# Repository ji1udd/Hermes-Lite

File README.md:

# <Font color="blue"> ji1udd Hermes-Lite Enhancement </font>
## 6M Frontend using undersampling technique  
Hermes-Lite v1.22 covers HF all bands.
Its sampling frequency(Fs) is 73.728MHz and the first nyquist zone is under 36.764MHz.
Hermes-Lite is a good performance system, but It does not support 6M band. 
I thought whether Hermes-Lite could be used on 6M band by using undersampling technique, without a transverter. 
But I have never seen any undersampling transmitters and transcevers.
I made 6M Test Frontend board for the performance test and to realized it. 

[_Schematic_](6M-Band/frontend_6M_v100/docs/frontend6m.pdf)
[_BOM_](6M-Band/frontend_6M_v100/docs/BOM_Frontend6m.pdf)
[_Gerber_](6M-Band/frontend_6M_v100/gerber/frontend6.zip)
[_Gerber-ReadMe_](6M-Band/frontend_6M_v100/gerber/ReadMe.txt)  
[_PCB Errata and filter adjustment_](6M-Band/frontend_6M_v100/docs/Frontend6m_v1.0_PCB_Errata_and_FilterAdjustment.pdf)

I got very good result. Here is the output power and IMD3 of 6M Test Frontend. 

This application takes advantage of 1st image signal ( Fs-Ftx ). 
Therefore, AD9866 interpolation should be off (1x).   

Other unnecessary spurs (e.g. 2Ftx) should be care.
In case of Hermes-Lite v1.22,  Fs is 73.728MHz. 2Ftx is out of 6M band. 2Ftx spur can be rejected by BPF perfectly.  

If Fs is 76.8MHz (Hermes-Lite v2 will use), 2Fx is in-band. 
It might be weak (<-65dBc) according to the current result.
But Fs=76.8MHz settign is not suitable for 6M.  

For more detail, refer to [_6M Support thread_](https://groups.google.com/forum/#!topic/hermes-lite/oetsCIdmZzY).

## Frontend v1.42 experiment with balanced 6M BPF.
I converted the single-ended 6M BPF that is used on 6M Frontend board to balanced-ended's in order to apply to Frontend v1.42 circuit.

I got the almost same result as 6M Frontend.

More result is [_here_.](6M-Band/frontend_v142_with_6M_filter/docs/6m_Spur_v142_and_orignal.pdf)

## Undersampling 6M transceiver (World's 1st?)
I made 6M transceiver using 6M Frontend. I added my new 6M power amplifier board. Its output power is 3W in CW.
In SSB mode, the output power should be kept under 1W for good IMD3 (under -35dBc) by adjusting Drive Level (TxPGA).
Rx Pre Amplifier on the schematic is not needed by adjusting AD9866 RxPGA.

[_Schematic_](6M-Band/PA_6M/docs/6mPA_v1.01.pdf)
[_BOM_](6M-Band/PA_6M/docs/BOM_6m_PA.pdf)
[_Gerber_] (6M-Band/PA_6M/gerber/amp6.zip)

## Audio Codec
As I have a sound trouble when PowerSDR VAC is used on my Windows8.1 PC, I added an external audio codec as a solid countermeasure.  
I got the audio codec information from [_ik1xpv web site_](http://www.steila.com/blog/index.php?controller=post&action=view&id_post=4).

[_Schematic_](audiocodec/docs/AudioCodec_v1.0.pdf)  
[_BOM_](audiocodec/docs/BOM_Keyer_AudioCodec.pdf)  
[_Gerber_](audiocodec/gerber/audiocodec.zip)  
[_Audio Codec board connection CVA9_](audiocodec/docs/Connector_Assignment_BeMicroCVA9_Keyer_AudioCodec.pdf)  
[_Mic jack jumper setting_](audiocodec/docs/Mic_Jack_jumper_setting.pdf)

Now, PowerSDR and piHPSDR works well with this audio codec board.

## Iambic keyer
I implemented  Iambic keyer functions that PowerSDR supports, except Keyer Mode-B. 
I implemented Keyer practice mode(Keyer is active, but does not transmit) instead of Mode-B. 
The keyer that I scratch built needs only 150 ALMs, 1 DSP block, 8K Byte block memory.

### Supported functions
- Variable Sidetone frequency :  
Sidetone is always synchronized with receiver pitch. I added two new ways of sidetone output.   
1) Square wave output for inexpensive piezo sounder.  
2) Sine wave output through an external audio codec.  
- Variable Speed control
- Others  
Keyer ON/OFF, Sidetone ON/OFF, Break in delay time, CW delay Key-Up,   
CW delay Key-Down,Reverse Paddles,Weight

[_Keyer installation diagram_](audiocodec/docs/IambicKeyer_installation_diagram.pdf)  
[_Keyer sequence and setting_](audiocodec/docs/Keyer_Sequece_and_setting.pdf)  
[_Modification of PCB (Schematic)_](audiocodec/docs/Modification_of_Audio_Codec_Board_for_keyer_schematic.pdf)  
[_Modification of PCB (photo)_](audiocodec/docs/Modification_of_Audio_Codec_Board_for_keyer.jpg)   
[_Keyer connection CVA9_](audiocodec/docs/Connector_Assignment_BeMicroCVA9_Keyer_AudioCodec.pdf)  
[_Keyer connection SDK (Not Verified Yet)_](audiocodec/docs/Connector_Assignment_BeMicroSDK_Keyer_AudioCodec.pdf)  

Verilog-HDL code was released on my git (27 July 2016).  

## Bemicro CVA9 100Base-TX connection
I modified the Hermes-Lite v1.22 firmware for connecting to Raspberry Pi / PiHPSDR directly. 

Verilog-HDL code was released on [_CVA9-100Base-TX branch_](https://github.com/ji1udd/Hermes-Lite/tree/CVA9-100Base-TX) (5 May 2017).

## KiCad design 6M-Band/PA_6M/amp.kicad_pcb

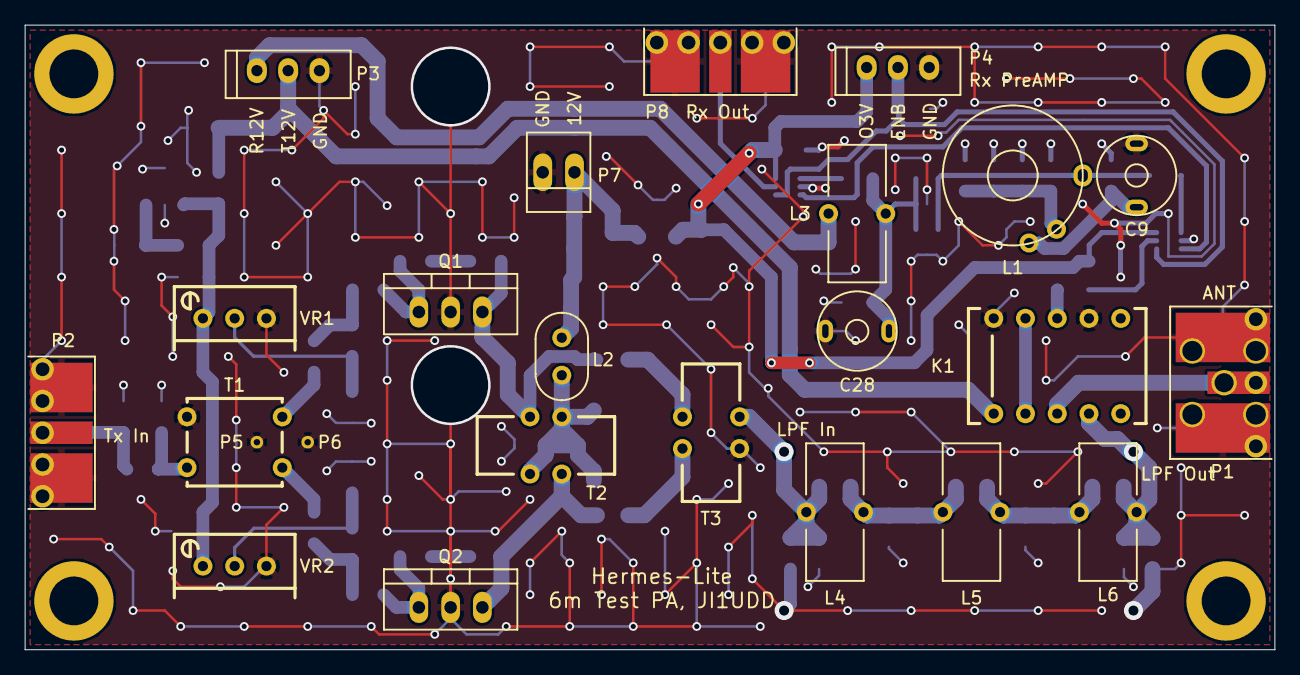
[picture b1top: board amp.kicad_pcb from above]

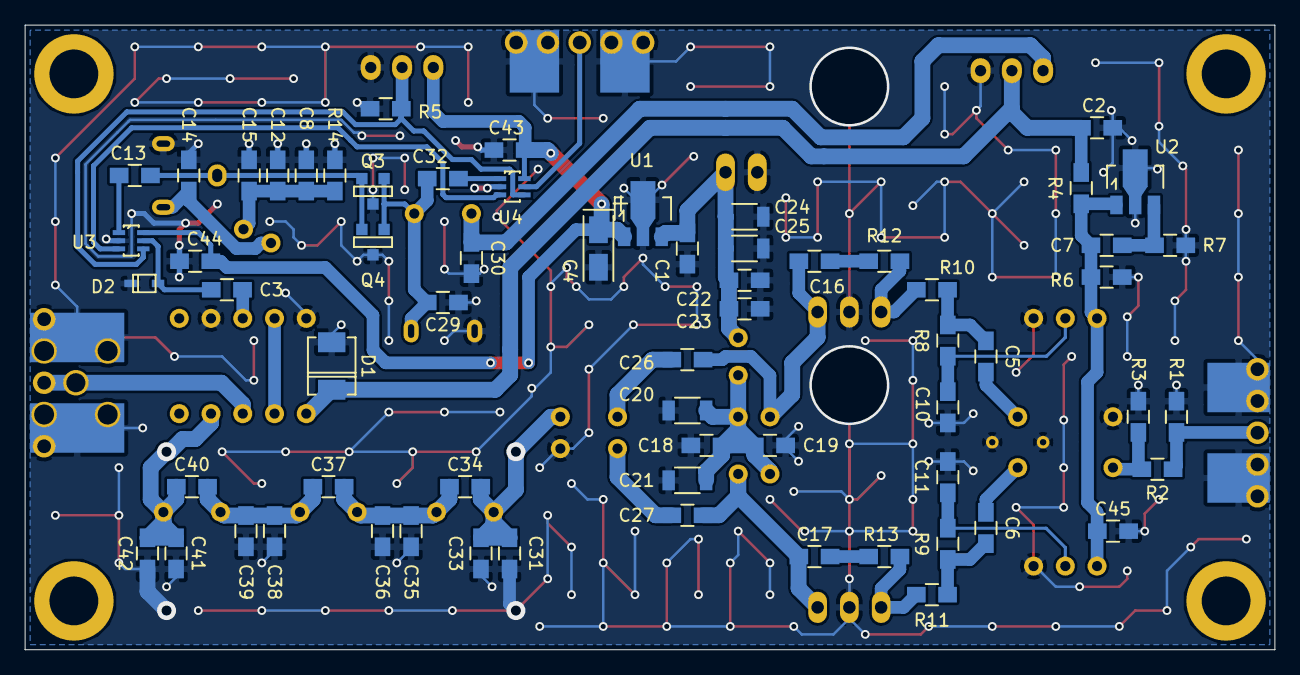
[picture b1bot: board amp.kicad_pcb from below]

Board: 2 copper layers, 99.9 x 50.0 mm, 93 parts (65 on the bottom side), 41 nets.

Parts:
C1: 330n; C_0805_HandSoldering
C2, C7: 1uF; C_0805_HandSoldering
C3, C5, C6, C8, C10, C11, C12, C13, C15, C18, C19, C22, C23, C26, C27, C30, C43, C44, C45: 10n; C_0805_HandSoldering
C4: 10u/10V; TantalC_SizeA_EIA-3216_Wave
C9, C28: 30p; TC_TZ03
C14, C29: 33p; C_0805_HandSoldering
C16, C17, C34, C36, C37, C39, C40: DNI; C_0805_HandSoldering
C20, C21, C24, C25: 22u; C_1206
C31, C33, C41, C42: 30p; C_0805_HandSoldering
C32: 27p; C_0805_HandSoldering
C35, C38: 120p; C_0805_HandSoldering
D1: 1N5819; DO-214AC(SMA)_12Swap
D2: CDSOD323-T05LC; SOD323
K1: EA2; Relay_EA2
L1: T37-10; T37_TP
L2: BN43-2402; BN43-2402_Choke
L3: T37-10; T37_SL
L4, L5, L6: T37-6; T37_SL
MH: VAL**; MH
MH#2, MH#3, MH#4: VAL**; MH
P1: Antenna; rfconnectorB-1
P2: TX IN; rfconnector
P3: Controlled PWR; JST_EH_3P
P4: PreAMP; JST_EH_3P
P5, P6: GND; via20
P7: 12V; PINHEAD1-2
P8: RX IN; rfconnector
Q1, Q2: RD06HHF1; TO-220_Neutral123_Vertical
Q3, Q4: MMBFJ310; SOT23-123
R1, R3, R12, R13: DNI; C_0805_HandSoldering
R2: 0; C_0805_HandSoldering
R4: 560; C_0805_HandSoldering
R5: 10k; C_0805_HandSoldering
R6: 4.7k; C_0805_HandSoldering
R7: 2.2k; C_0805_HandSoldering
R8, R9: 1k; C_0805_HandSoldering
R10, R11: 4.7; C_0805_HandSoldering
R14: 33; C_0805_HandSoldering
T1: BN43-2402; BN43-2402_TRNS
T2, T3: FT37-61; FT37_DF
U1: AN77L03M; SOT89-3_Housing
U2: TA76431F; SOT89-3_Housing
U3, U4: PE4259; pe4259
VR1, VR2: 10k; POT_3296W

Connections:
12V: C1.1, C22.1, C23.1, C24.1, C25.1, L2.2, P7.1, U1.3
/3V: C4.1, C43.1, C44.1, P4.1, U1.1, U3.6, U4.6
/8V: C7.1, C45.1, R4.1, R6.2, U2.1, VR1.1, VR2.1
/ANT: K1.3, P1.1
/LNA_In: C13.2, U3.1
/LNA_Out: C32.1, U4.1
/LPF_Out: C40.2, C41.1, C42.1, K1.4, L6.2
/PA_In: R2.1, R3.2, T1.1
/PA_Out: C31.1, C33.1, C34.1, L4.1, T3.3
GND: C1.2, C2.1, C4.2, C7.2, C8.2, C9.2, C10.2, C11.2, C12.2, C14.2, C15.2, C18.2, C19.2, C20.2, C21.2, C22.2, C23.2, C24.2, C25.2, C28.2, C29.2, C30.2, C31.2, C33.2, C35.2, C36.2, C38.2, C39.2, C41.2, C42.2, C43.2, C44.2, C45.2, D1.2, D2.2, K1.7, K1.10, P1.2, P2.2, P3.3, P4.3, P5.1, P6.1, P7.2, P8.2, Q1.2, Q2.2, Q3.3, Q4.3, R1.1, R3.1, R5.1, R7.1, R14.2, T1.2, T3.4, U1.2, U2.2, U3.2, U4.2, VR1.3, VR2.3
unnamed: C3.1, K1.8
unnamed: C3.2, D2.1, U3.5
unnamed: C5.1, R8.2, R10.2
unnamed: C5.2, T1.4
unnamed: C6.1, T1.3
unnamed: C6.2, R9.1, R11.2
unnamed: C10.1, R8.1, VR1.2
unnamed: C11.1, R9.2, VR2.2
unnamed: C8.1, C12.1, C15.1, L1.2, R14.1
unnamed: C13.1, L1.3, Q3.2, Q4.2
unnamed: C9.1, C14.1, L1.1
unnamed: C16.1, R12.1
unnamed: C16.2, C26.1, Q1.3, T2.2
unnamed: C17.1, R13.1
unnamed: C17.2, C27.1, Q2.3, T2.3
unnamed: C18.1, C19.1, C20.1, C21.1, L2.1, T2.1, T2.4
unnamed: C26.2, T3.1
unnamed: C27.2, T3.2
unnamed: C28.1, C29.1, C32.2, L3.1, Q3.1, Q4.1
unnamed: C34.2, C35.1, C36.1, C37.1, L4.2, L5.1
unnamed: C37.2, C38.1, C39.1, C40.1, L5.2, L6.1
unnamed: K1.2, K1.9
unnamed: P2.1, R1.2, R2.2
unnamed: P4.2, R5.2, U3.4, U4.4
unnamed: P8.1, U4.5
unnamed: Q1.1, R10.1, R12.2
unnamed: Q2.1, R11.1, R13.2
unnamed: R6.1, R7.2, U2.3
unnamed: U3.3, U4.3
R12V: C30.1, L3.2, P3.1
T12V: C2.2, D1.1, K1.1, P3.2, R4.2

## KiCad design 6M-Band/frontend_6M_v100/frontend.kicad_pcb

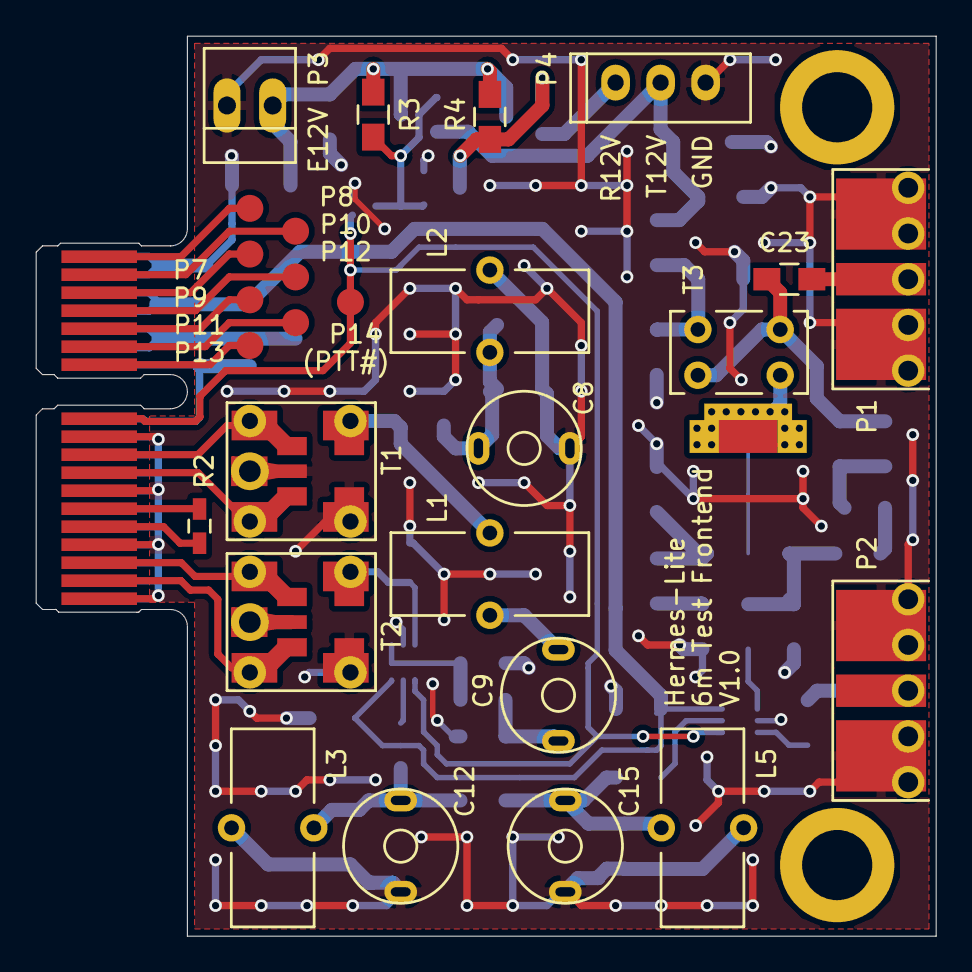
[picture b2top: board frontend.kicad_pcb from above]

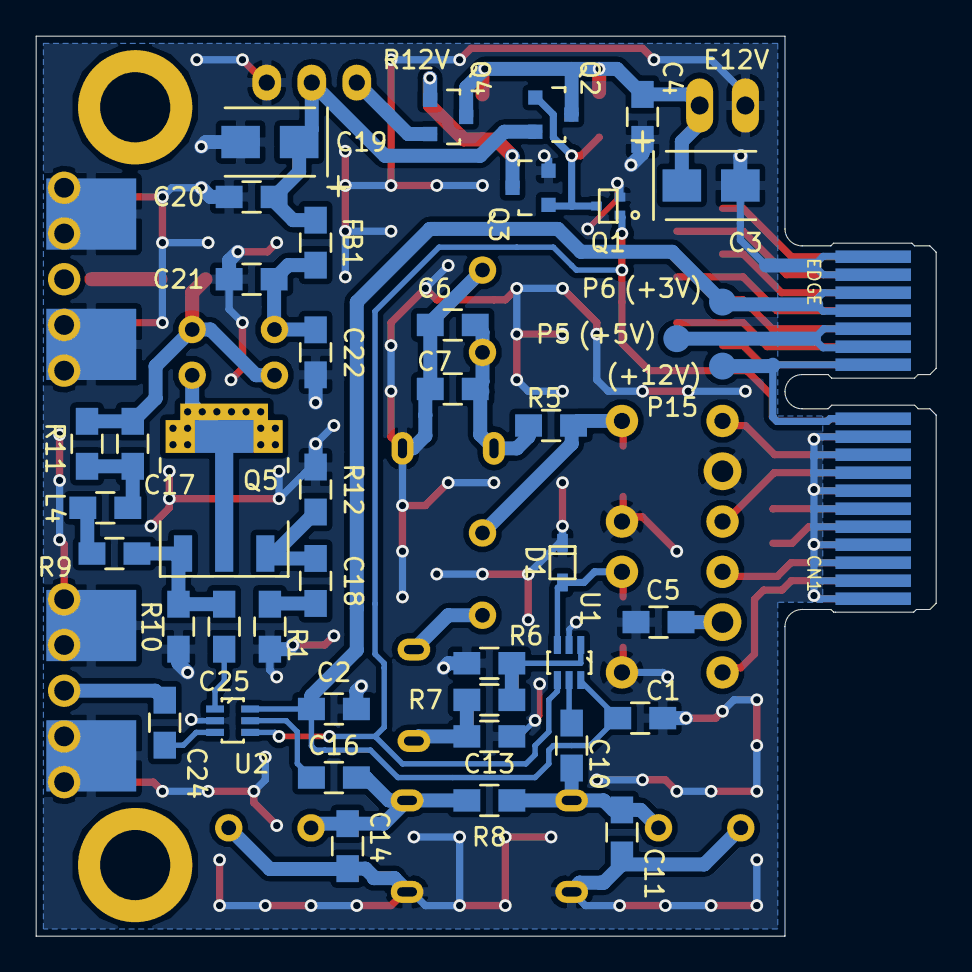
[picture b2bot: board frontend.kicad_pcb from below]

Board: 2 copper layers, 50.0 x 50.0 mm, 75 parts (46 on the bottom side), 49 nets.

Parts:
C1, C2, C4, C5, C17, C18, C20, C22, C23, C24, C25: 10n; C_0805_HandSoldering
C3, C19: 10u/16V; TantalC_SizeB_EIA-3528_Wave
C6: 150p; C_0805_HandSoldering
C7: 22p; C_0805_HandSoldering
C8, C12, C15: 30p; TC_TZ03
C9: 20p; TC_TZ03
C10, C16: 10p; C_0805_HandSoldering
C11, C14: 33p; C_0805_HandSoldering
C13: 1.8p; C_0805_HandSoldering
C21: 100n; C_0805_HandSoldering
CN1: EDGE
D1: DIODESCH2; SOD323
DMY1, DMY2, DMY3: DMY; Dummy
FB1: FB; C_0805_HandSoldering
L1, L2, L3, L5: T37-6; T37_SL
L4: LK2125R68; C_0805_HandSoldering
MH: MH2; MH
MH#2: MH1; MH
P1, P2: SMA; rfconnector
P3: 12V; PINHEAD1-2
P4: CONN_01X03; JST_EH_3P
P5: TST5; Measurement_Point_Round-SMD-Pad_Small
P6, P7, P8, P9, P10, P11, P12, P13, P14, P15: TST3; Measurement_Point_Round-SMD-Pad_Small
Q1: DTC144E; SOT416
Q2, Q4: IRLML6402; SOT-23
Q3: 2N7002; SOT-23
Q5: PZT2222A; SOT-223-Heat
R1, R12: 27; C_0805_HandSoldering
R2: DNI; C_0603_HandSoldering
R3, R4: 10k; C_0805_HandSoldering
R5: 51; C_0805_HandSoldering
R6, R8: DNI; C_0805_HandSoldering
R7: 0; C_0805_HandSoldering
R9: 390; C_0805_HandSoldering
R10: 820; C_0805_HandSoldering
R11: 3.9k; C_0805_HandSoldering
T1: 1:1; TRANSFSMT
T2: 9:1; TRANSFSMT
T3: BN43-2402; BN2402_BF
U1, U2: PE4259; pe4259

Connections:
3V: C1.1, C2.1, CN1.A15, CN1.A16, P6.1, U1.6, U2.6
5V: CN1.A13, CN1.A14, P5.1
12V: CN1.A11, CN1.A12, P15.1
/E12V: C3.1, C4.1, P3.1, Q2.3, Q4.3, R3.2, R4.2
/R12V: P4.1, Q4.2
GND: C1.2, C2.2, C3.2, C4.2, C5.2, C8.2, C12.2, C15.2, C19.2, C20.2, C21.2, C22.2, CN1.A1, CN1.A2, CN1.A3, CN1.A4, CN1.A5, CN1.A6, CN1.A7, CN1.A8, CN1.A9, CN1.A10, CN1.A17, CN1.A18, CN1.B1, CN1.B4, CN1.B7, CN1.B10, D1.2, DMY1.1, DMY2.1, DMY3.1, P1.2, P2.2, P3.2, P4.3, Q1.2, Q3.2, R1.1, R6.1, R8.1, R10.1, R12.1, T1.2, T1.4, T2.4, U1.2, U2.2
unnamed: C5.1, T2.2
unnamed: C6.1, C7.1, C8.1, L2.1, R5.2
unnamed: C6.2, C7.2, DMY1.2, L2.2
unnamed: C9.1, L1.2
unnamed: C9.2, R7.2, R8.2
unnamed: C10.1, C11.1, C12.1, C13.2, L3.1
unnamed: C10.2, U1.5
unnamed: C11.2, DMY2.2, L3.2
unnamed: C13.1, C14.1, C15.1, C16.2, L5.1
unnamed: C14.2, DMY3.2, L5.2
unnamed: C16.1, U2.5
unnamed: C17.1, C23.2, R11.2, T3.2, T3.3
unnamed: C17.2, L4.2, R11.1
unnamed: C18.1, Q5.3, R12.2
unnamed: C18.2, R1.2
unnamed: C21.1, C22.1, FB1.1, T3.4
unnamed: C23.1, P1.1
unnamed: C24.1, P2.1
unnamed: C24.2, U2.3
unnamed: C25.1, Q5.1, R9.1, R10.2
unnamed: C25.2, U2.1
unnamed: CN1.B2, T2.3
unnamed: CN1.B3, T2.1
unnamed: CN1.B5, R2.1
unnamed: CN1.B6, R2.2
unnamed: CN1.B8, T1.3
unnamed: CN1.B9, T1.1
unnamed: CN1.B12, P13.1
unnamed: CN1.B13, P12.1
unnamed: CN1.B14, P11.1
unnamed: CN1.B15, P10.1
unnamed: CN1.B16, P9.1
unnamed: CN1.B17, P8.1
unnamed: CN1.B18, P7.1
unnamed: D1.1, T2.5, U1.3
unnamed: L1.1, R5.1, T1.5
unnamed: L4.1, R9.2
unnamed: Q1.3, Q2.1, Q3.1, R3.1
unnamed: Q3.3, Q4.1, R4.1
unnamed: Q5.2, T3.1
unnamed: R6.2, R7.1, U1.1
T12V: C19.1, C20.1, FB1.2, P4.2, Q2.2
TX: CN1.B11, P14.1, Q1.1, U1.4, U2.4

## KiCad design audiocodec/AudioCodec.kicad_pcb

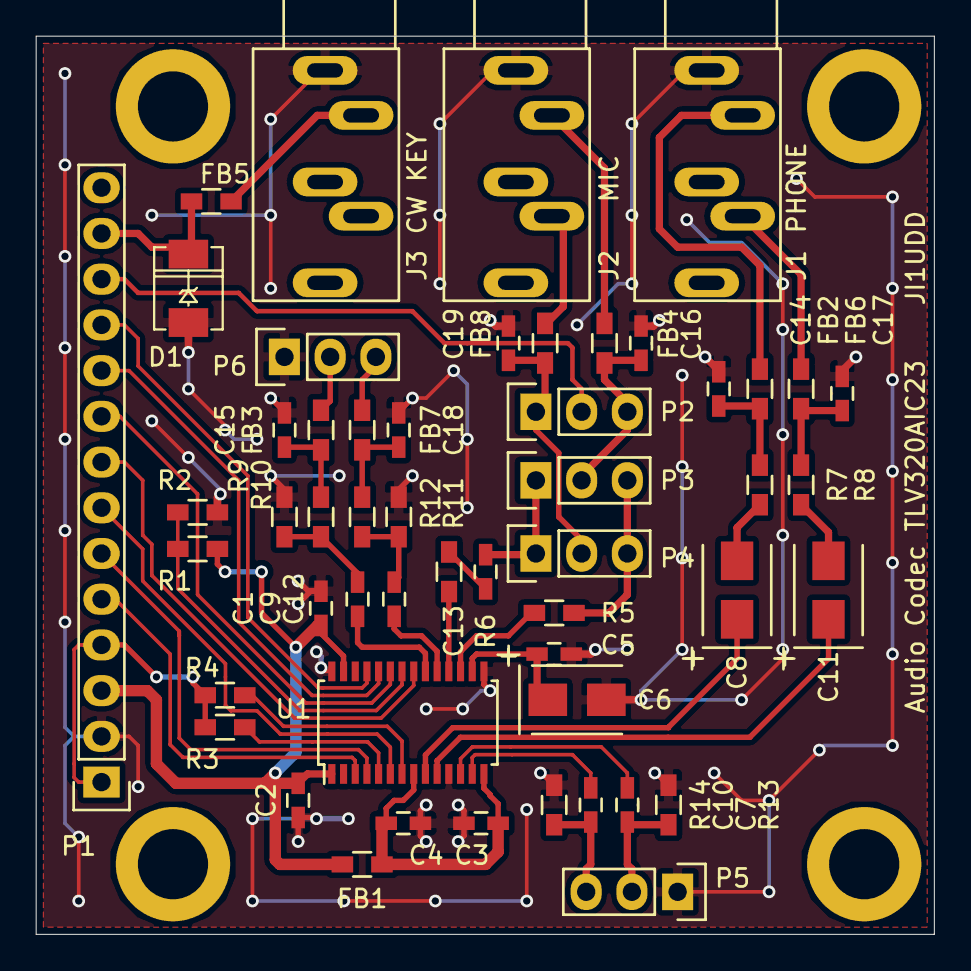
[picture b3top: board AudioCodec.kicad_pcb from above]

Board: 2 copper layers, 49.9 x 49.9 mm, 56 parts (0 on the bottom side), 47 nets.

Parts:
C1, C2, C3, C4, C5: 100n; C_0603_HandSoldering
C6, C8, C11: 10u; TantalC_SizeB_EIA-3528_Wave
C7, C9, C10, C12, C13: 1u; C_0603_HandSoldering
C14, C15, C16, C17, C18, C19: 4.7n; C_0603_HandSoldering
D1: DIODESCH2; DO-214AC(SMA)
FB1, FB2, FB3, FB4, FB5, FB6, FB7, FB8: FB; R_0603_HandSoldering
J1, J2, J3: PJ325; JACK_PJ325
MH: VAL**; MH
MH#2, MH#3, MH#4: VAL**; MH
P1: CONN_01X14; Pin_Header_Straight_1x14
P2, P3, P4, P5, P6: CONN_01X03; Pin_Header_Straight_1x03
R1: 1k; R_0603_HandSoldering
R2: DNI; R_0603_HandSoldering
R3, R4: 150; R_0603_HandSoldering
R5: 3.3k; R_0603_HandSoldering
R6, R9, R10, R11, R12: 4.7k; R_0603_HandSoldering
R7, R8: 100; R_0603_HandSoldering
R13, R14: 100k; R_0603_HandSoldering
U1: TLV320AIC23BPW; TSSOP-28_4.4x9.7mm_Pitch0.65mm

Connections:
+3V3: C1.1, C2.1, FB1.2, P1.3, R1.1, U1.1, U1.27
//PTT: P1.12, P2.2
/MODE: R1.2, R2.1, U1.22
GND: C1.2, C2.2, C3.1, C4.1, C5.2, C6.2, C14.2, C15.2, C16.2, C17.2, C18.2, C19.2, D1.1, J1.1, J2.1, J3.1, P1.2, P5.1, P6.1, R2.2, R9.2, R11.2, R13.2, R14.2, U1.11, U1.15, U1.28
unnamed: C3.2, C4.2, FB1.1, U1.8, U1.14
unnamed: C5.1, C6.1, U1.16
unnamed: C7.1, U1.12
unnamed: C7.2, P5.2, R13.1
unnamed: C8.1, U1.9
unnamed: C8.2, R7.2
unnamed: C9.1, U1.20
unnamed: C9.2, R9.1, R10.2
unnamed: C10.1, U1.13
unnamed: C10.2, P5.3, R14.1
unnamed: C11.1, U1.10
unnamed: C11.2, R8.2
unnamed: C12.1, U1.19
unnamed: C12.2, R11.1, R12.2
unnamed: C13.1, R6.1
unnamed: C13.2, P3.1, P4.1
unnamed: C14.1, FB2.1, R7.1
unnamed: C15.1, FB3.1, R10.1
unnamed: C16.1, FB4.1, P2.3, P3.2
unnamed: C17.1, FB6.1, R8.1
unnamed: C18.1, FB7.1, R12.1
unnamed: C19.1, FB8.1, P2.1, P4.2
unnamed: D1.2, FB5.1, P1.13
unnamed: FB2.2, J1.5
unnamed: FB3.2, P6.2
unnamed: FB4.2, J2.5
unnamed: FB5.2, J3.5
unnamed: FB6.2, J1.3
unnamed: FB7.2, P6.3
unnamed: FB8.2, J2.3
unnamed: P1.1, P1.4, R3.2, R4.2
unnamed: P1.5, U1.3
unnamed: P1.6, U1.4
unnamed: P1.7, U1.6
unnamed: P1.8, U1.21
unnamed: P1.9, U1.23
unnamed: P1.10, U1.24
unnamed: P1.11, U1.25
unnamed: P3.3, P4.3, R5.1
unnamed: R3.1, U1.5
unnamed: R4.1, U1.7
unnamed: R5.2, U1.17
unnamed: R6.2, U1.18

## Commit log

2016-07-26 added Keyer and AudioCodec
2016-07-26 added Keyer and AudioCodec (new files)
2016-07-26 added 6M Test Frontend/Transceiver, AudioCodec and Iambic Keyer documents
2016-07-26 fixed typo
2017-05-04 modified for CVA9 100Base-TX
2017-05-05 Added CVA9 100Base-TX connection
2017-05-05 Fixed READ.MD syntax
2018-01-13 modified for HLv2 RxGAIN compatibility
2018-01-21 Added external AMP and Tuner support function
2018-01-21 Revert "Added external AMP and Tuner support function"
    This reverts commit 9a47e8ed3f24216532109cfd67d8305784a1342f.
